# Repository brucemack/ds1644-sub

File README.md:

Overview
========
The goal of this project is to produce an adaptor board to allow a "modern" M48T35 NVRAM/RTC chip to be 
used where a
"vintage" DS1643/DS1644 used to be.  This is relevant for owners of S-COM
5K/6K/7K repeater controllers.  The old Dallas Semi parts are
hard to find in DIP format, and at this point their batteries are likely 
dead.

(Testing is still in process - more documentation will follow if this works.)

Here's what the board looks like:

References
==========

* [M48T35 Datasheet](https://www.st.com/content/ccc/resource/technical/document/datasheet/group1/b6/56/b6/36/4d/38/4d/18/CD00000551/files/CD00000551.pdf/jcr:content/translations/en.CD00000551.pdf)
* [DS1643 Datasheet](https://www.analog.com/media/en/technical-documentation/data-sheets/DS1643-DS1643P.pdf) - used in the 5K
* [DS1644 Datasheet](https://www.analog.com/media/cn/technical-documentation/data-sheets/2744.pdf) - used in the 7K

Photograph of DS1643 in an S-COM 5K to demonstrate that mechanical clearance isn't an issue around the chip.

Notes on Testing an Original DS1643
===================================

I have access to an S-COM 5K that has a DS1643 NVRAM/RTC chip in it. I've been using that 
to do some testing.  I pulled the DS1643 out of the controller and put it into my memory tester (see more detail on that below). 

The date code on the part is 1996.  It works fine!

This chip is interesting in that the RTC is mapped into the 
very top few bytes of the NVRAM.  On the 8K part you need to read from locations 0x1ff9 to 0x1fff to get the time/date.  IMPORTANT: Remember that all numbers are in 
BCD format with the 1's digit in the low-order nibble and the 10's digit in the high-order nibble of each byte.

When I powered up the chip and read the time from the magic 
locations I was amazed to see that it was correct to within <2 hours after an unknown period
of time of non-use. Obviously, the battery is still good in this 
particular unit. :-)

The S-COM 7K uses a 32K part. Everything should be the same,
except the memory map locations of the RTC are higher.

Notes Related to a Memory Tester
================================

A memory testing device was created to read/write/validate 5V RAM/PROM parts, along with any related adaptor boards. This could be used to test
that a chip/socket is working correctly or to make a copy of an NVRAM/EPROM/EEPROM. 

The tester can support 16 address lines, 8 bit-directional data lines, and three control lines (~OE, ~WE, ~CS, etc),
for a total of 27 signals.  Only 6 GPIO pins on a microcontroller are needed to drive the tester.

The testing cycle writes/reads different patterns into the 
memory chip to make sure there are no bad bits.

Here's what the tester PCB looks like:

Here it is wired into an Arduino Nano and a 28-pin ZIF socket
for testing:

Here's a vintage [Toshiba 2K SRAM chip](http://matthieu.benoit.free.fr/cross/data_sheets/TMM2016AP.pdf) that was tested successfully:

Judging from [this databook](http://www.bitsavers.org/components/toshiba/_dataBook/1983_Toshiba_MOS_Memory.pdf) an the date code
on that chip I'm assuming it's a 1984 part.  We've come a long
way in 40 years!

Tester Shift Register Chain Layout
----------------------------------
       
       |    Control     |   Address Low   |  Address High   |    Data Out     |   Data In      |
       +----------------+-----------------+-----------------+-----------------+----------------+
        C C C x x x x O   A A A A A A A A   A A A A A A A A   O O O O O O O O   I I I I I I I I  
        0 1 2         E   0 0 0 0 0 0 0 0   0 0 1 1 1 1 1 1   0 1 2 3 4 5 6 7   0 1 2 3 4 5 6 7
                          0 1 2 3 4 5 6 7   8 9 0 1 2 3 4 5

                                    =========== DATA FLOW ==========>    

Notes
* Data flows from left to right.
* There is no hand-off between O7 and I0.
* The high-order bit of the Control register (OE) controls the -OE of the Data Out register. So
you must write a zero into this bit when generating a write into a memory device.

Tester Control Interface
------------------------

(From left to right)

* Pin 1: Data Out - High-order bit out of the Data In register (i.e. I7 in the above diagram)
* Pin 2: Data In - Low-order bit into the Control register (i.e. C0 in the above diagram)
* Pin 3: Latch In (+) - Only relevant for the Data In register.  Rising edge locks the memory device output 
into the Data In register.  Make sure that shift/load is set to 1 before doing this.
* Pin 4: Shift/Load - Only relevant for the Data In register.  Issue a zero pulse after the Latch In clock
to move data into the shift register, preparing to shift out the data that was read.
* Pin 5: Clock (+) - Rising edge shifts one position to the right.  Make sure that shift/load is set to 0 before
doing this.
* Pin 6: Latch Out (+) - Rising edge makes the contents of the Control, Address Low, Address High, and Data Out
registers visible to the memory device.  
* Pin 7: 5V
* Pin 8: Ground

Copyright
=========

Copyright (C) 2024 - Bruce MacKinnon

This work is covered under the terms of the GNU Public License (V3). Please consult the LICENSE file for more information.

This work is being made available for non-commercial use. Redistribution, commercial use or sale of any part is prohibited.

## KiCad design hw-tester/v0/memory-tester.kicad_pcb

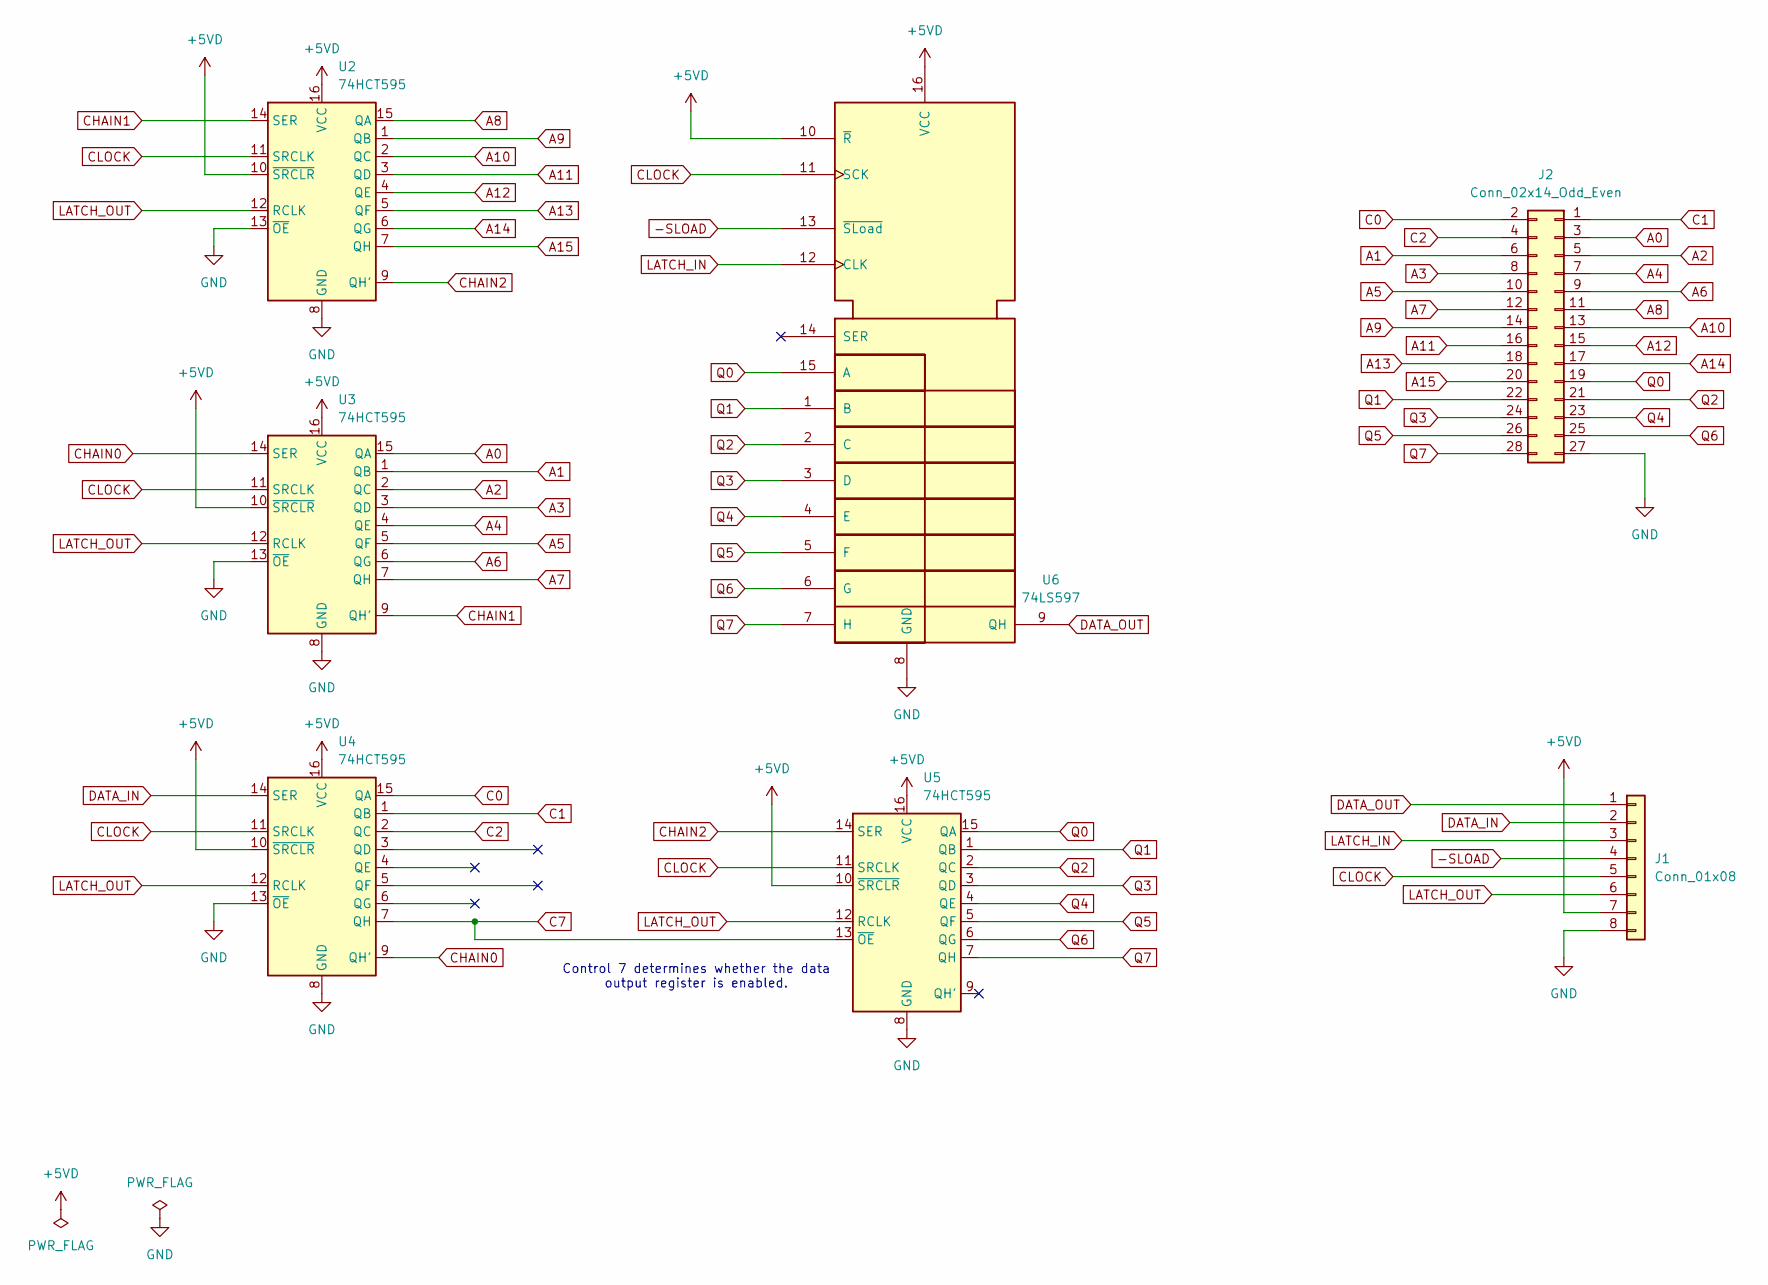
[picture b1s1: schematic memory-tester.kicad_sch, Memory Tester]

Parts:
J1: Conn_01x08; PinHeader_1x08_P2.54mm_Vertical
J2: Conn_02x14_Odd_Even; PinSocket_2x14_P2.54mm_Vertical
U2, U3, U4, U5: 74HCT595; TSSOP-16_4.4x5mm_P0.65mm; LCSC C273642
U6: 74LS597; TSSOP-16_4.4x5mm_P0.65mm; LCSC C5444304

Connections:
+5VD: J1.7, U2.10 (~SRCLR), U2.16 (VCC), U3.10 (~SRCLR), U3.16 (VCC), U4.10 (~SRCLR), U4.16 (VCC), U5.10 (~SRCLR), U5.16 (VCC), U6.10 (~R), U6.16 (VCC)
-SLOAD: J1.4, U6.13 (~SLoad)
A0: J2.3, U3.15 (QA)
A1: J2.6, U3.1 (QB)
A2: J2.5, U3.2 (QC)
A3: J2.8, U3.3 (QD)
A4: J2.7, U3.4 (QE)
A5: J2.10, U3.5 (QF)
A6: J2.9, U3.6 (QG)
A7: J2.12, U3.7 (QH)
A8: J2.11, U2.15 (QA)
A9: J2.14, U2.1 (QB)
A10: J2.13, U2.2 (QC)
A11: J2.16, U2.3 (QD)
A12: J2.15, U2.4 (QE)
A13: J2.18, U2.5 (QF)
A14: J2.17, U2.6 (QG)
A15: J2.20, U2.7 (QH)
C0: J2.2, U4.15 (QA)
C1: J2.1, U4.1 (QB)
C2: J2.4, U4.2 (QC)
C7: U4.7 (QH), U5.13 (~OE)
CHAIN0: U3.14 (SER), U4.9 (QH')
CHAIN1: U2.14 (SER), U3.9 (QH')
CHAIN2: U2.9 (QH'), U5.14 (SER)
CLOCK: J1.5, U2.11 (SRCLK), U3.11 (SRCLK), U4.11 (SRCLK), U5.11 (SRCLK), U6.11 (SCK)
DATA_IN: J1.2, U4.14 (SER)
DATA_OUT: J1.1, U6.9 (QH)
GND: J1.8, J2.27, U2.8 (GND), U2.13 (~OE), U3.8 (GND), U3.13 (~OE), U4.8 (GND), U4.13 (~OE), U5.8 (GND), U6.8 (GND)
LATCH_IN: J1.3, U6.12 (CLK)
LATCH_OUT: J1.6, U2.12 (RCLK), U3.12 (RCLK), U4.12 (RCLK), U5.12 (RCLK)
Q0: J2.19, U5.15 (QA), U6.15 (A)
Q1: J2.22, U5.1 (QB), U6.1 (B)
Q2: J2.21, U5.2 (QC), U6.2 (C)
Q3: J2.24, U5.3 (QD), U6.3 (D)
Q4: J2.23, U5.4 (QE), U6.4 (E)
Q5: J2.26, U5.5 (QF), U6.5 (F)
Q6: J2.25, U5.6 (QG), U6.6 (G)
Q7: J2.28, U5.7 (QH), U6.7 (H)

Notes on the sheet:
Control 7 determines whether the data output register is enabled.

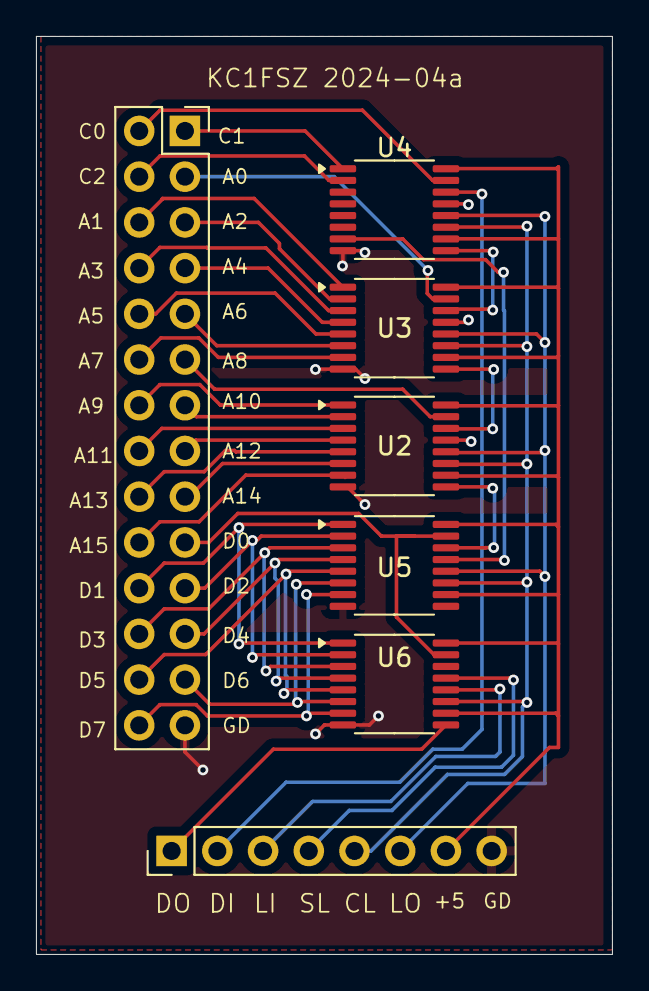
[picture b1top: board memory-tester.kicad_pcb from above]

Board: 2 copper layers, 32.0 x 51.0 mm, 7 parts (0 on the bottom side), 39 nets.

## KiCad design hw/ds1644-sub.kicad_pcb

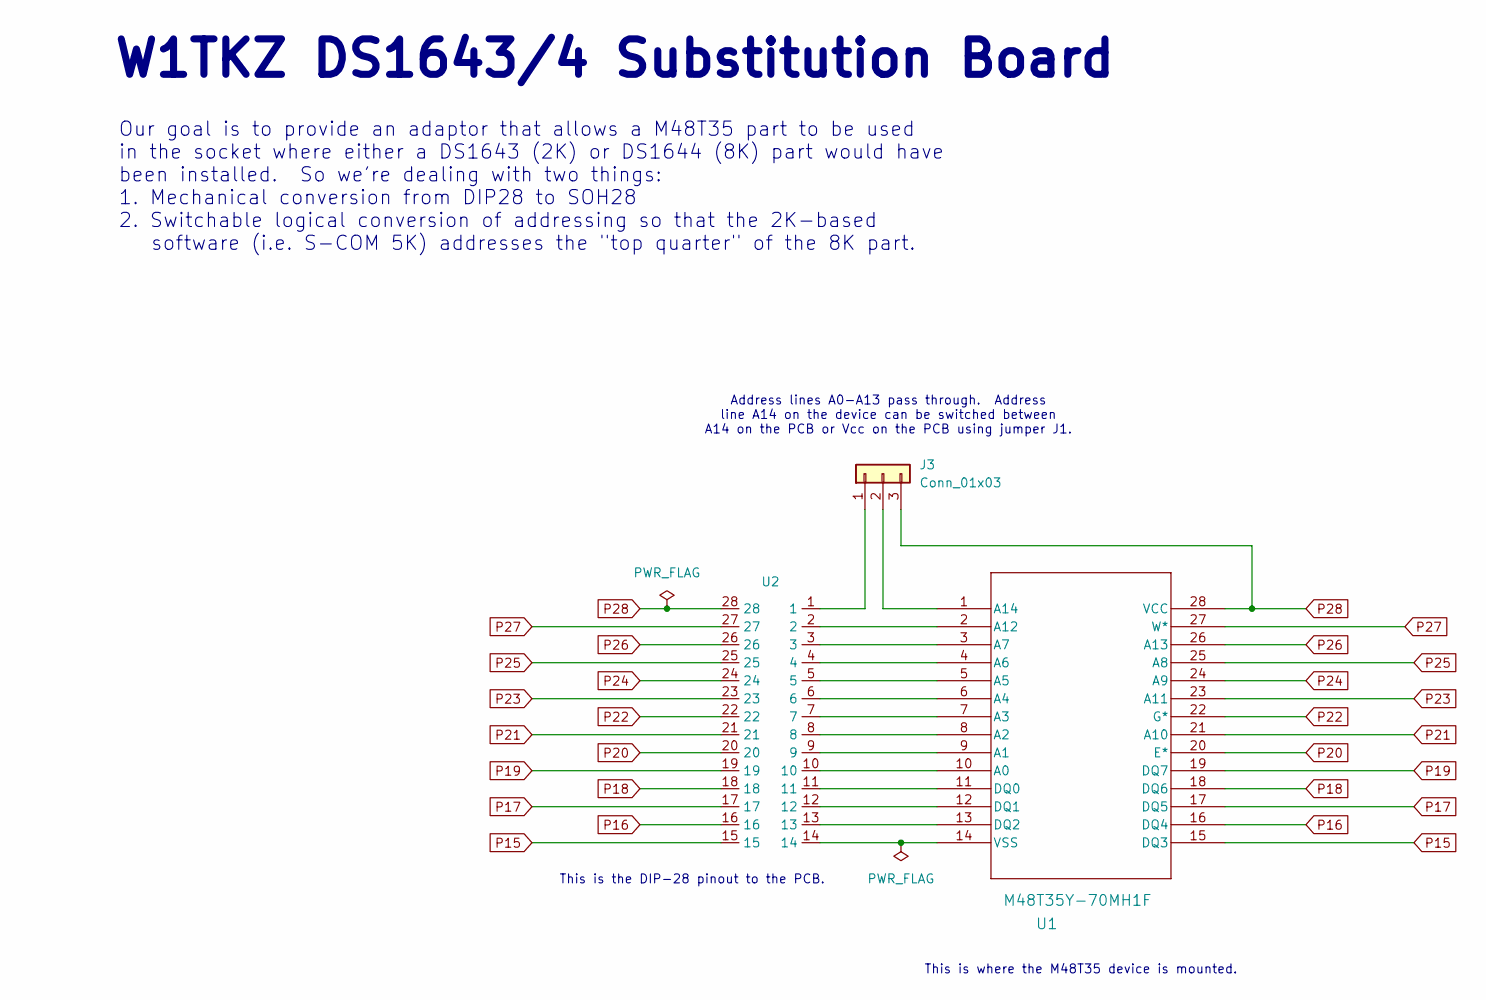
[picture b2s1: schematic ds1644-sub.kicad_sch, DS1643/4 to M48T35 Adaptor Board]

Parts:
J3: Conn_01x03; PinHeader_1x03_P2.54mm_Vertical
U1: M48T35Y-70MH1F; SOH28_STM
U2: DIP-28-SMD

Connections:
unnamed: J3.1, U2.1
unnamed: J3.2, U1.1 (A14)
unnamed: U1.10 (A0), U2.10
unnamed: U1.9 (A1), U2.9
unnamed: U1.8 (A2), U2.8
unnamed: U1.7 (A3), U2.7
unnamed: U1.6 (A4), U2.6
unnamed: U1.5 (A5), U2.5
unnamed: U1.4 (A6), U2.4
unnamed: U1.3 (A7), U2.3
unnamed: U1.2 (A12), U2.2
unnamed: U1.11 (DQ0), U2.11
unnamed: U1.12 (DQ1), U2.12
unnamed: U1.13 (DQ2), U2.13
unnamed: U1.14 (VSS), U2.14
P15: U1.15 (DQ3), U2.15
P16: U1.16 (DQ4), U2.16
P17: U1.17 (DQ5), U2.17
P18: U1.18 (DQ6), U2.18
P19: U1.19 (DQ7), U2.19
P20: U1.20 (E*), U2.20
P21: U1.21 (A10), U2.21
P22: U1.22 (G*), U2.22
P23: U1.23 (A11), U2.23
P24: U1.24 (A9), U2.24
P25: U1.25 (A8), U2.25
P26: U1.26 (A13), U2.26
P27: U1.27 (W*), U2.27
P28: J3.3, U1.28 (VCC), U2.28

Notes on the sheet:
W1TKZ DS1643/4 Substitution Board
Our goal is to provide an adaptor that allows a M48T35 part to be used in the socket where either a DS1643 (2K) or DS1644 (8K) part would have been installed. So we're dealing with two things: 1. Mechanical conversion from DIP28 to SOH28 2. Switchable logical conversion of addressing so that the 2K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
This is where the M48T35 device is mounted.
Address lines A0-A13 pass through. Address line A14 on the device can be switched between A14 on the PCB or Vcc on the PCB using jumper J1.
This is the DIP-28 pinout to the PCB.

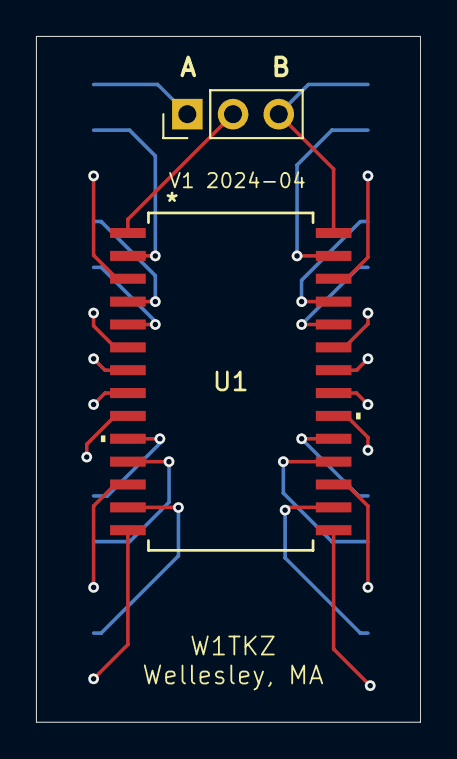
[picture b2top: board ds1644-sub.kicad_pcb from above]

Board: 2 copper layers, 21.3 x 38.1 mm, 3 parts (1 on the bottom side), 29 nets.

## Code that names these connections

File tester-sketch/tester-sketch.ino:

/**
 * Copyright (C) 2024, Bruce MacKinnon KC1FSZ
 *
 * This program is free software: you can redistribute it and/or modify
 * it under the terms of the GNU General Public License as published by
 * the Free Software Foundation, either version 3 of the License, or
 * (at your option) any later version.
 *
 * This program is distributed in the hope that it will be useful,
 * but WITHOUT ANY WARRANTY; without even the implied warranty of
 * MERCHANTABILITY or FITNESS FOR A PARTICULAR PURPOSE.  See the
 * GNU General Public License for more details.
 *
 * You should have received a copy of the GNU General Public License
 * along with this program.  If not, see <https://www.gnu.org/licenses/>.
 *
 * FOR AMATEUR RADIO USE ONLY.
 * NOT FOR COMMERCIAL USE WITHOUT PERMISSION.
 */
#define PIN_DATA_OUT (2)
#define PIN_DATA_IN (3)
#define PIN_LATCH_IN (4)
#define PIN_SHIFT_LOAD (5)
#define PIN_CLOCK (6)
#define PIN_LATCH_OUT (7)
#define PIN_LED (13)

// TEMP: DUE TO HW BUG
#define PIN_MEM_OE (8)
#define PIN_MEM_WE (9)

/*
 * Shifts 32 bits into the control, address (2), and data registers.
 */
void writeRaw(uint32_t v) {
  // Shift each bit into the ring
  for (int i = 0; i < 32; i++) {  
    // Setup a data bit
    digitalWrite(PIN_DATA_IN, (v & 0x80000000) ? 1 : 0);
    // Shift clock
    digitalWrite(PIN_CLOCK, 1);
    digitalWrite(PIN_CLOCK, 0);
    // Rotate 
    v = v << 1;

    // TEMP (DUE TO HARDWARE BUG)
    // Latch out
    digitalWrite(PIN_LATCH_OUT, 1);
    digitalWrite(PIN_LATCH_OUT, 0);   
  }
  // Latch out
  //digitalWrite(PIN_LATCH_OUT, 1);
  //digitalWrite(PIN_LATCH_OUT, 0);   
}

uint8_t readRaw() {
  // Load parallel data into latch
  digitalWrite(PIN_LATCH_IN, 1);
  digitalWrite(PIN_LATCH_IN, 0);     
  // Transfer latch data to shift register
  digitalWrite(PIN_SHIFT_LOAD, 0);
  // Prepare to start shifting
  digitalWrite(PIN_SHIFT_LOAD, 1);
  uint8_t result = 0;
  // Shift each bit from the ring
  for (int i = 0; i < 8; i++) {
    // Rotate
    result = result << 1;  
    if (digitalRead(PIN_DATA_OUT) == HIGH)
      result |= 1;
    // Shift clock
    digitalWrite(PIN_CLOCK, 1);
    digitalWrite(PIN_CLOCK, 0);
  }
  return result;
}

void writeMem(uint16_t addr, uint8_t data) {
  // OE=0
  uint32_t ring = ((uint32_t)addr << 8) | ((uint32_t)data << 24);
  writeRaw(ring);
  // Strobe ~WE
  digitalWrite(PIN_MEM_WE, 0);
  digitalWrite(PIN_MEM_WE, 1);  
}

uint8_t readMem(uint16_t addr) {
  // OE=1 to prevent the Data Out register from interfering
  uint32_t ring = ((uint32_t)addr << 8) | (0b10000000);
  writeRaw(ring);
  // Enable memory output
  digitalWrite(PIN_MEM_OE, 0);
  delay(1);
  // Read back
  uint8_t r = readRaw();
  // Disable memory output
  digitalWrite(PIN_MEM_OE, 1);  
  return r;
}

void setup() {

  // Console
  Serial.begin(9600);

  pinMode(PIN_LED, OUTPUT);
  pinMode(PIN_DATA_OUT, INPUT);
  pinMode(PIN_DATA_IN, OUTPUT);
  pinMode(PIN_LATCH_IN, OUTPUT);
  digitalWrite(PIN_LATCH_IN, 0);
  pinMode(PIN_SHIFT_LOAD, OUTPUT);
  digitalWrite(PIN_SHIFT_LOAD, 1);
  pinMode(PIN_CLOCK, OUTPUT);
  digitalWrite(PIN_CLOCK, 0);
  pinMode(PIN_LATCH_OUT, OUTPUT);
  digitalWrite(PIN_LATCH_OUT, 0);

  // TEMP: WILL BE MOVED TO CONTROL REGISTER
  pinMode(PIN_MEM_OE, OUTPUT);
  digitalWrite(PIN_MEM_OE, 1);
  pinMode(PIN_MEM_WE, OUTPUT);
  digitalWrite(PIN_MEM_WE, 1);
  // TEMP: WILL BE MOVED TO CONTROL REGISTER

  // Diag
  digitalWrite(PIN_LED, 1);
  delay(500);
  digitalWrite(PIN_LED, 0);
  delay(500);
  digitalWrite(PIN_LED, 1);

  Serial.println("Memory Tester V0");

  uint16_t space = 2048;
  Serial.print("Checking ");
  Serial.print(space);
  Serial.println(" locations ...");
  
  bool failed = false;
  for (uint16_t a = 0; a < space; a++) {
    writeMem(a, 0x55);
    uint8_t t0 = readMem(a);
    writeMem(a, 0xaa);
    uint8_t t1 = readMem(a);
    if (t0 != 0x55 || t1 != 0xaa) {
      Serial.print("Bad location: ");
      Serial.println(a);
      failed = true;
      break;  
    }
  }
  for (uint16_t a = 0; a < space; a++)
    writeMem(a, a);
  for (uint16_t a = 0; a < space; a++)
    if (readMem(a) != (a & 0xff)) {
      Serial.print("Bad location: ");
      Serial.println(a);
      failed = true;
      break;        
    } 
  if (!failed) {
    Serial.println("No faults detected");
  }
}

void loop() {
  /*  
  // Write a C0=1, disable OE
  writeRaw(0b110000000);
  // Read back
  uint32_t r = readRaw();
  Serial.print(r);
  Serial.println();
  delay(1000);
  
  // Write a C0=0, disable OE
  writeRaw(0b010000000);
  // Read back
  r = readRaw();
  Serial.print(r);
  Serial.println();
  delay(1000);
  */
  /*
  // Internal self-test
  // Show that we can latch data out and read it back
  // Write DO=0x55, enable OE
  writeRaw(0x00ff0000);
  // Read back
  uint32_t r = readRaw();
  Serial.print(r);
  Serial.println();
  delay(1000);
  
  // Write DO=0xaa, enable OE
  writeRaw(0x00000000);
  // Read back
  r = readRaw();
  Serial.print(r);
  Serial.println();
  delay(1000);
  */
}

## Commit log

2024-04-13 Working
2024-04-22 Added docs for tester
2024-04-22 Initial demo of memory tester
2024-04-23 Tester is working (with SW work-around for HW bug)
2024-04-23 Cleaned up a HW bug in the tester, provided docs
2024-04-24 Updated docs

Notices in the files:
hw-tester/v0/memory-tester.kicad_pcb:
Copyright (c) 2024 - NOT FOR COMMERCIAL USE
